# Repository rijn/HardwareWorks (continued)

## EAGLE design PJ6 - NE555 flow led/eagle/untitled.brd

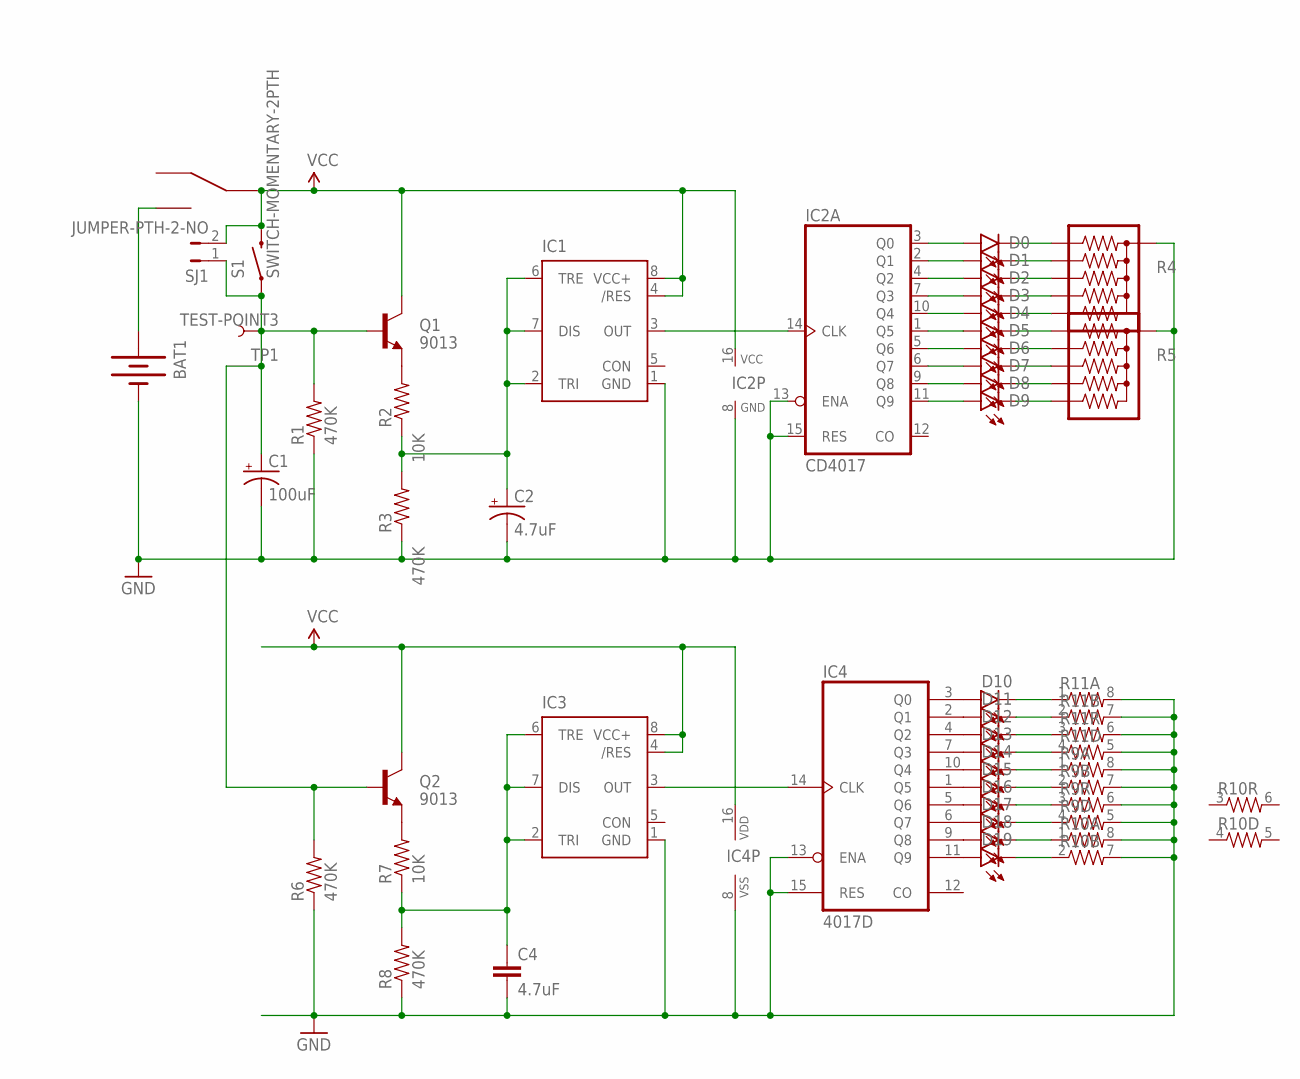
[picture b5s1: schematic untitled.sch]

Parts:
BAT1: BATTERY20PTH; BATTCOM_20MM_PTH
C1: 100uF; CPOL-RADIAL-100UF-25V
C2: 4.7uF; CPOL-RADIAL-100UF-25V
C4: 4.7uF; 0603-CAP
D0, D1, D2, D3, D4, D5, D6, D7, D8, D9: LED3MM
D10, D11, D12, D13, D14, D15, D16, D17, D18, D19: LED1206; LED-1206
IC1: NE555KIT; DIP08-KIT
IC2: CD4017; DIL16-KIT
IC3: NE555D; SO08
IC4: 4017D; SO16
Q1: 9013; TO-92-AMMO
Q2: 9013; SOT23-3
R1, R3: 470K; AXIAL-0.1
R2: 10K; AXIAL-0.1
R4, R5: RPACK-BUSSED-5-SIP-PTH-5; RPACK-SIP-PTH-5
R6, R8: 470K; 0603-RES
R7: 10K; 0603-RES
R9, R10, R11: RESISTOR-ARRAY0603-ARV; 0603-ARV
S1: SWITCH-MOMENTARY-2PTH; TACTILE-PTH
SJ1: JUMPER-PTH-2-NO; PTH-JUMPER-2-NO_NO_SILK
TP1: TEST-POINT3; PAD.03X.03
U$1: KFT; SWITCH_LOCK

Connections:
GND: BAT1.2 (-), C1.2 (-), C2.2 (-), C4.2, IC1.1 (GND), IC2.8 (GND), IC2.13 (ENA), IC2.15 (RES), IC3.1 (GND), IC4.8 (VSS), IC4.13 (ENA), IC4.15 (RES), R1.P$1 (1), R3.P$1 (1), R4.P$1 (1), R5.P$1 (1), R6.1, R8.1, R9.5 (2), R9.6 (2), R9.7 (2), R9.8 (2), R10.7 (2), R10.8 (2), R11.5 (2), R11.6 (2), R11.7 (2), R11.8 (2)
unnamed: D10.A, IC4.3 (Q0)
unnamed: C1.1 (+), Q1.2 (B), Q2.1 (B), R1.P$2 (2), R6.2, S1.1, SJ1.1, TP1.P$1
unnamed: Q2.2 (E), R7.2
unnamed: Q1.1 (E), R2.P$2 (2)
unnamed: C2.1 (+), IC1.2 (TRI), IC1.6 (TRE), IC1.7 (DIS), R2.P$1 (1), R3.P$2 (2)
unnamed: C4.1, IC3.2 (TRI), IC3.6 (TRE), IC3.7 (DIS), R7.1, R8.2
unnamed: IC3.3 (OUT), IC4.14 (CLK)
unnamed: D11.A, IC4.2 (Q1)
unnamed: D0.A, IC2.3 (Q0)
unnamed: D1.A, IC2.2 (Q1)
unnamed: D12.A, IC4.4 (Q2)
unnamed: D2.A, IC2.4 (Q2)
unnamed: IC1.3 (OUT), IC2.14 (CLK)
unnamed: D13.A, IC4.7 (Q3)
unnamed: D14.A, IC4.10 (Q4)
unnamed: D15.A, IC4.1 (Q5)
unnamed: D16.A, IC4.5 (Q6)
unnamed: D17.A, IC4.6 (Q7)
unnamed: D18.A, IC4.9 (Q8)
unnamed: D3.A, IC2.7 (Q3)
unnamed: D4.A, IC2.10 (Q4)
unnamed: D5.A, IC2.1 (Q5)
unnamed: D6.A, IC2.5 (Q6)
unnamed: D7.A, IC2.6 (Q7)
unnamed: D8.A, IC2.9 (Q8)
unnamed: D9.A, IC2.11 (Q9)
unnamed: D0.K (C), R4.P$2 (2)
unnamed: D1.K (C), R4.P$3 (3)
unnamed: D2.K (C), R4.P$4 (4)
unnamed: D3.K (C), R4.P$5 (5)
unnamed: D4.K (C), R4.P$6 (6)
unnamed: D5.K (C), R5.P$2 (2)
unnamed: D6.K (C), R5.P$3 (3)
unnamed: D7.K (C), R5.P$4 (4)
unnamed: D8.K (C), R5.P$5 (5)
unnamed: D9.K (C), R5.P$6 (6)
unnamed: D19.A, IC4.11 (Q9)
unnamed: BAT1.1 (+), U$1.S$3, U$1.S$4
unnamed: D10.C, R11.1
unnamed: D11.C, R11.2 (1)
unnamed: D12.C, R11.3 (1)
unnamed: D13.C, R11.4 (1)
unnamed: D14.C, R9.1
unnamed: D15.C, R9.2 (1)
unnamed: D16.C, R9.3 (1)
unnamed: D17.C, R9.4 (1)
unnamed: D18.C, R10.1
unnamed: D19.C, R10.2 (1)
VCC: IC1.4 (/RES), IC1.8 (VCC+), IC2.16 (VCC), IC3.4 (/RES), IC3.8 (VCC+), IC4.16 (VDD), Q1.3 (C), Q2.3 (C), S1.3 (2), SJ1.2, U$1.S$2 (P$C), U$1.S$5 (P$C)

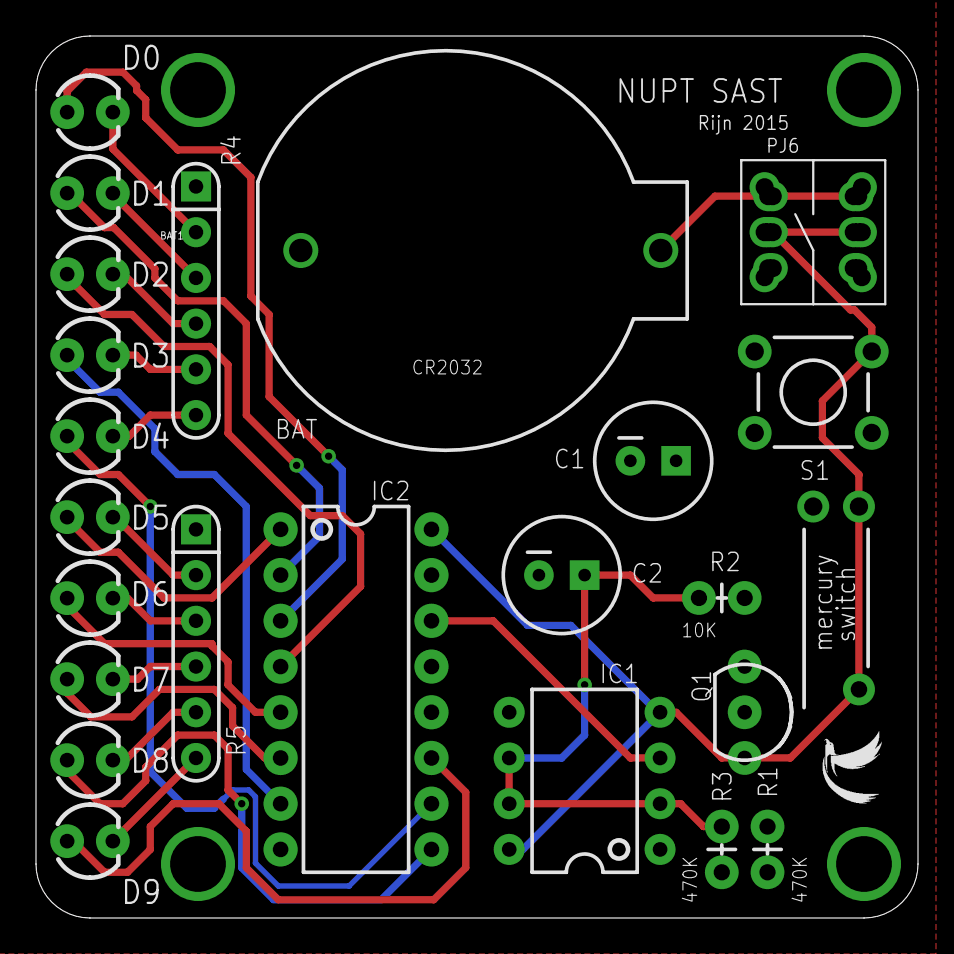
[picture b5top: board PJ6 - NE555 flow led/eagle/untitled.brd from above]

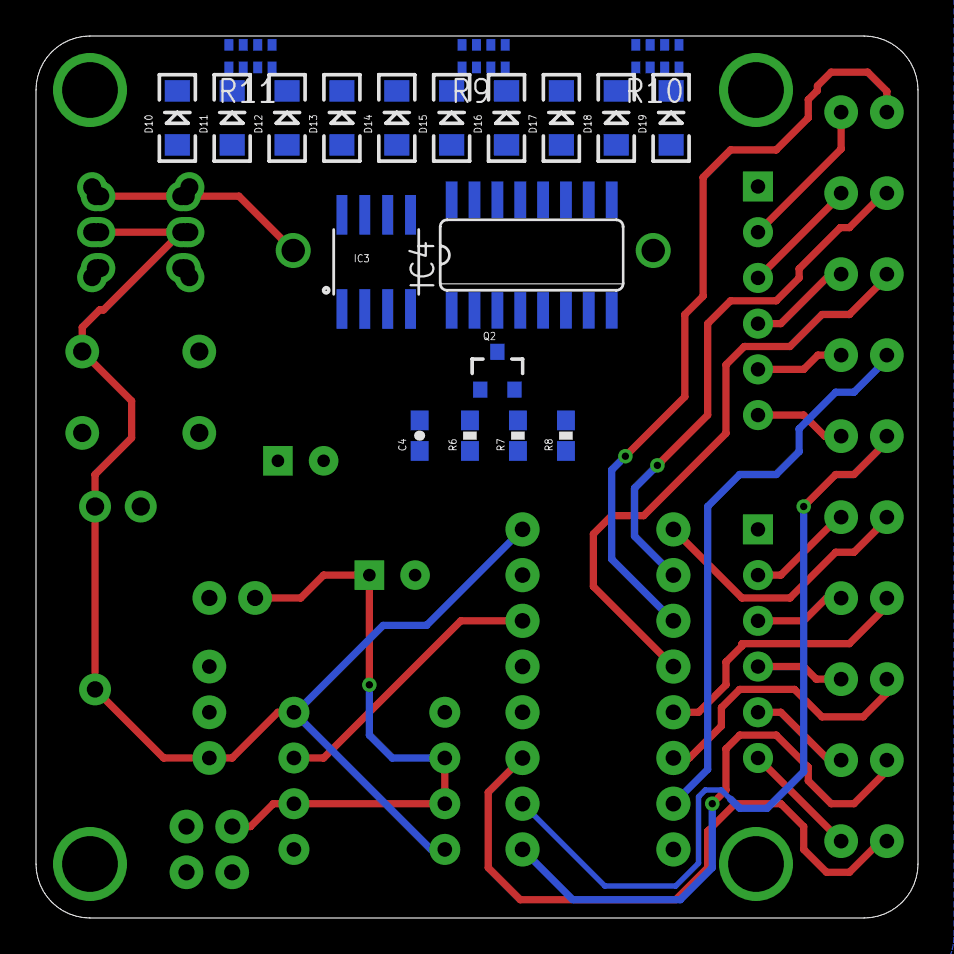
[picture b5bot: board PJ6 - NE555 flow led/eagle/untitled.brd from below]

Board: 2 copper layers, 49.0 x 49.0 mm, 46 parts (21 on the bottom side), 50 nets.

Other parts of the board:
U$2: LOGO

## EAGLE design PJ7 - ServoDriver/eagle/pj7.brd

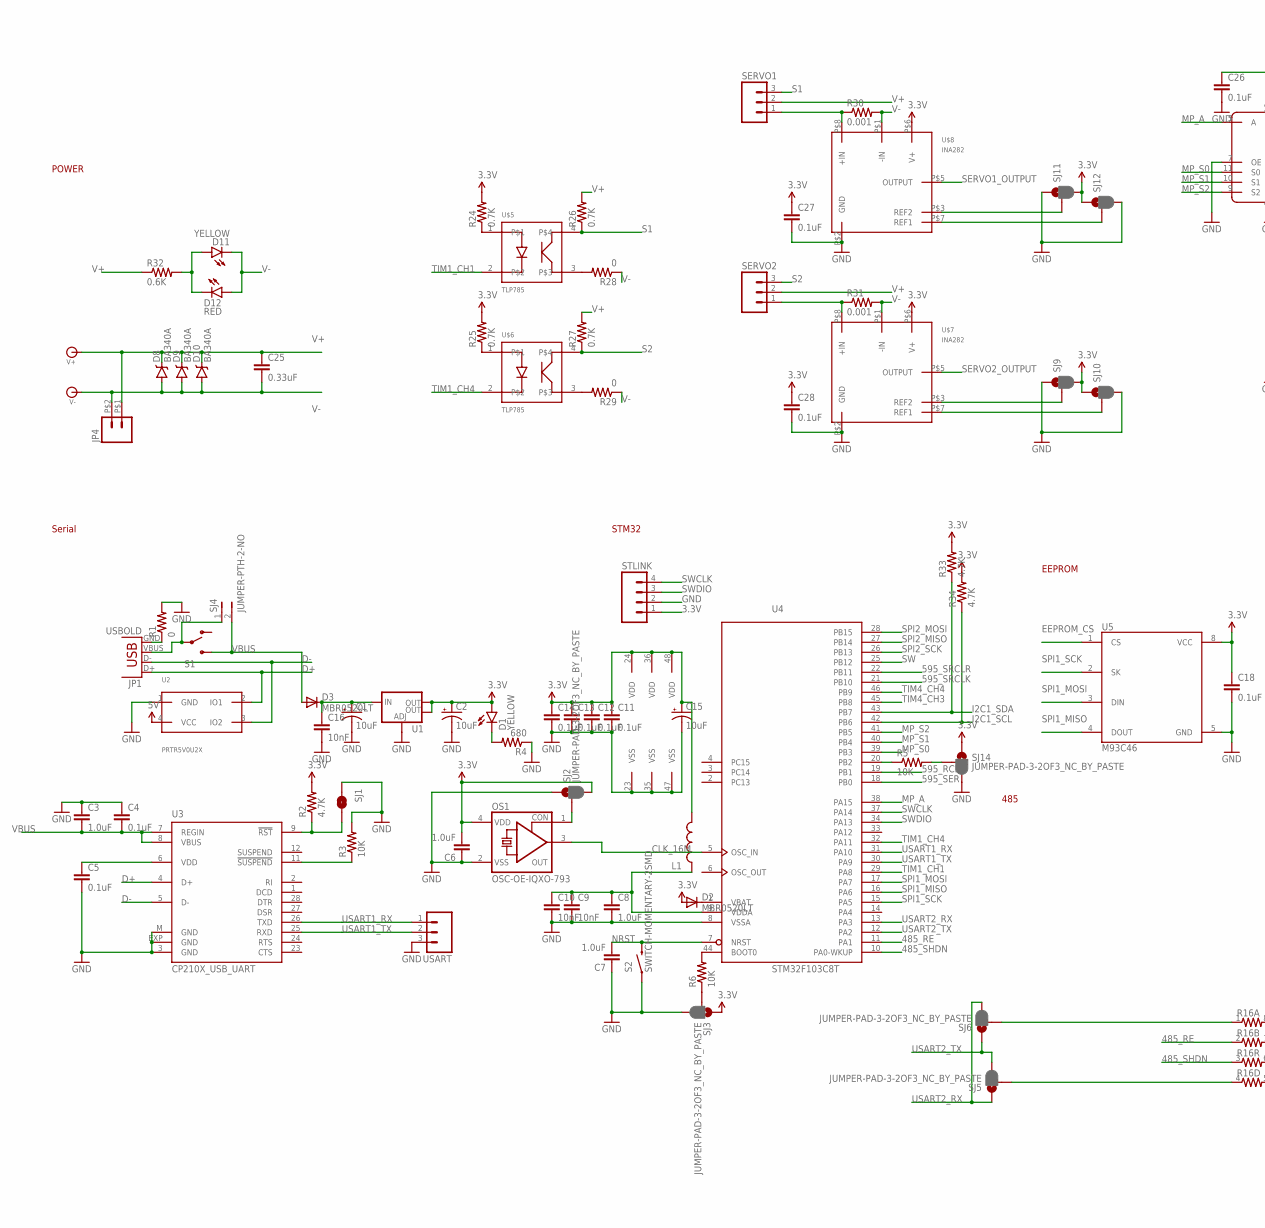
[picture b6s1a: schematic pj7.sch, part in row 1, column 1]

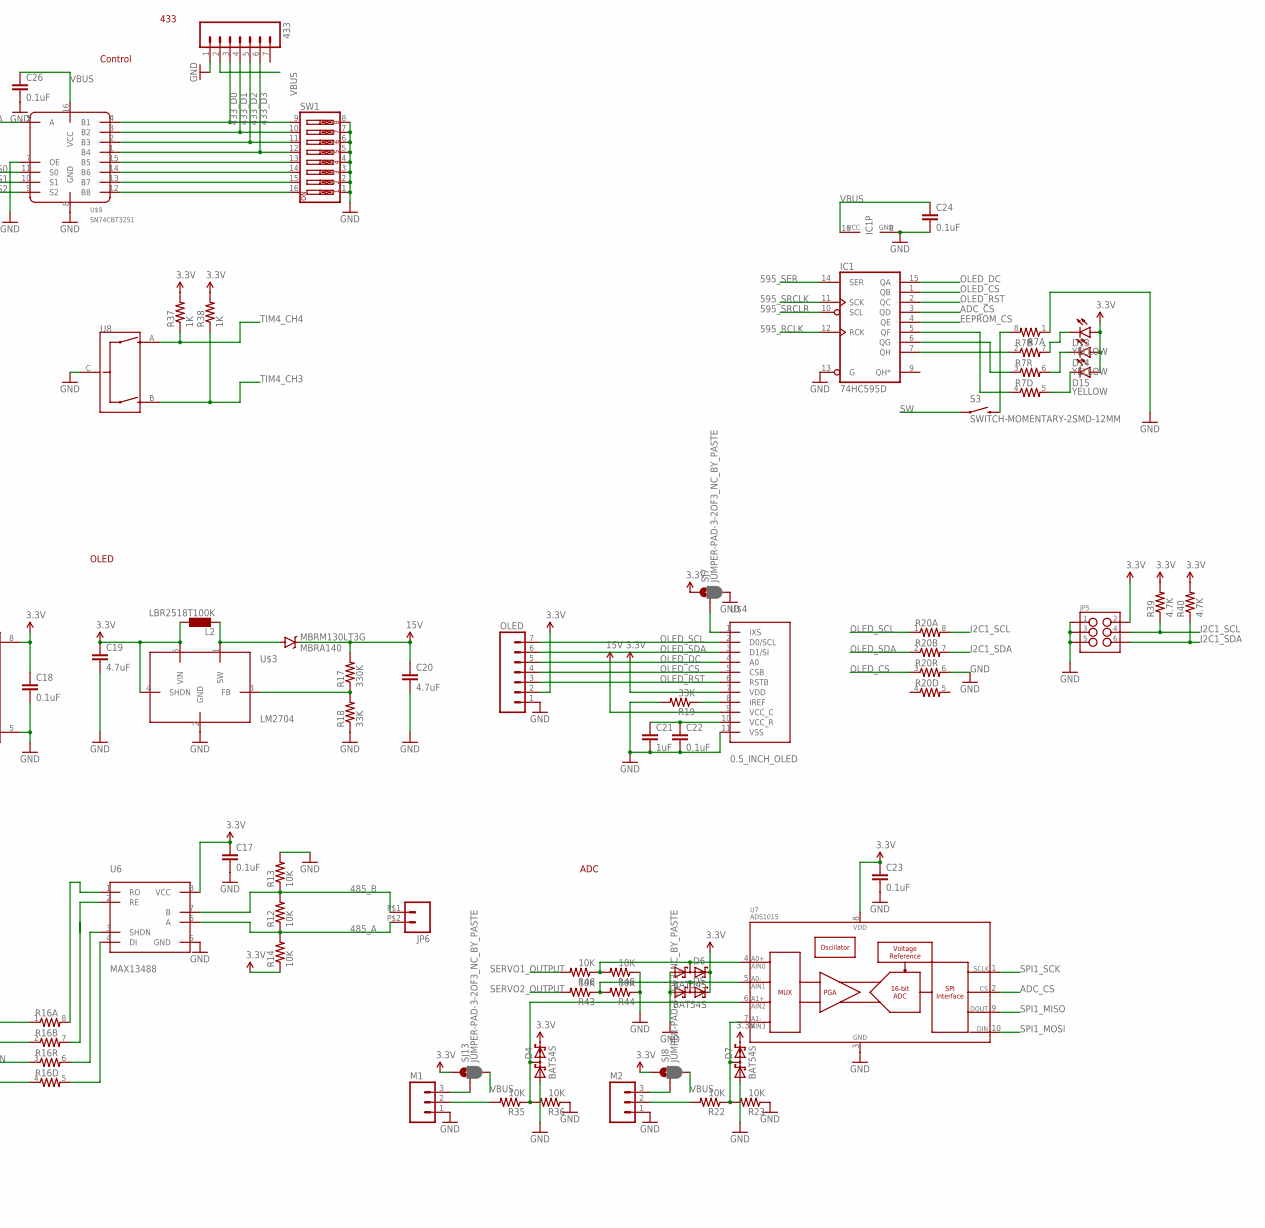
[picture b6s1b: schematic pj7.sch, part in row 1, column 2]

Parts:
433: M07LOCK; 1X07_LOCK
C1, C2, C15: 10uF; EIA3216
C3, C6, C7, C8: 1.0uF; 0603-CAP
C4, C5, C11, C12, C13, C14, C17, C18, C22, C23, C24, C26, C27, C28: 0.1uF; 0603-CAP
C9, C10, C16: 10nF; 0603-CAP
C19, C20: 4.7uF; 0603-CAP
C21: 1uF; 0603-CAP
C25: 0.33uF; 0805-CAP
D1, D11, D13, D14, D15: YELLOW; LED-1206
D2, D3: MBR0520LT; SOD123
D4, D5, D6, D7: BAT54S; SOT23
D8, D9, D10: BA340A; SMA-DIODE
D12: RED; LED-1206
IC1: 74HC595D; SO16
JP1: USBOLD; USB-MINIB-OLD
JP4, JP6: M02; 1X02_5.08
JP5: M03X2; 2X3_SMD
L1: INDUCTOR0603; 0603
L2: LBR2518T100K; L3225P
M1, M2: M03LOCK; 1X03_LOCK
MBRM130LT3G: MBRA140; SMA-DIODE
OLED: M07LOCK; 1X07_LOCK
OS1: OSC-OE-IQXO-793; 2.5X2-4-PAD
R1, R28, R29: 0; 0603
R2, R33, R34, R39, R40: 4.7K; 0603-RES
R3, R5, R6, R12, R13, R14, R22, R23, R35, R36, R43, R44, R45, R46: 10K; 0603-RES
R4: 680; 0603-RES
R7, R16, R20: RESISTOR-ARRAY0603-ARV; 0603-ARV
R17: 330K; 0603-RES
R18, R19: 33K; 0603-RES
R24, R25, R26, R27: 0.7K; 0603
R30, R31: 0.001; 2512
R32: 0.6K; 0805
R37, R38: 1K; 0603-RES
S1: SWITCH-SPDTSMD; AYZ0202
S2: SWITCH-MOMENTARY-2SMD; TACTILE-SWITCH-SMD
S3: SWITCH-MOMENTARY-2SMD-12MM; TACTILE-SMD-12MM
SERVO1, SERVO2: M03LOCK_LONGPADS; 1X03_LOCK_LONGPADS
SJ1: JUMPER-PAD-2-NOYES_SILK; PAD-JUMPER-2-NO_YES_SILK
SJ2, SJ3, SJ5, SJ6, SJ7, SJ8, SJ9, SJ10, SJ11, SJ12, SJ13, SJ14: JUMPER-PAD-3-2OF3_NC_BY_PASTE; PAD-JUMPER-3-2OF3_NC_BY_PASTE_YES_SILK_FULL_BOX
SJ4: JUMPER-PTH-2-NO; PTH-JUMPER-2-NO_NO_SILK
STLINK: M04LOCK; 1X04_LOCK
SW1: SW_DIP-8-SMT-HALFSIZE; DIPSWITCH-08-50MIL
U1: V_REG_LM1117SOT223; SOT223
U2: PRTR5V0U2X; SOT143
U3: CP210X_USB_UART; MLP28
U4: STM32F103C8T; LQFP48
U5: M93C46; SO08
U6: MAX13488; SOIC8
U7: ADS1015; MSOP10
U8: ENCODER-QUADRATURE; ENCODER-16MM-QUAD
U$3: LM2704; SOT23-5
U$4: 0.5_INCH_OLED; BL125-11RL-TAGF
U$5, U$6: TLP785; DIL04
U$7, U$8: INA282; SOP8
U$9: SN74CBT3251; TSSOP16
USART: M03LOCK; 1X03_LOCK
V+: BANANA_CONN
V-: BANANA_CONN

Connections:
3.3V: C2.A (+), C6.2, C11.1, C12.1, C13.1, C14.1, C15.A (+), C17.1, C18.1, C19.1, C23.1, C27.1, C28.1, D1.A, D2.A, D4.2 (C2), D5.2 (C2), D6.2 (C2), D7.2 (C2), D13.A, D14.A, D15.A, JP5.2, L1.2, L2.1, OLED.2, OS1.4 (VDD), R2.2, R14.1, R24.2, R25.2, R33.2, R34.2, R37.2, R38.2, R39.2, R40.2, SJ2.3, SJ3.1, SJ7.1, SJ8.1, SJ9.3, SJ10.1, SJ11.3, SJ12.1, SJ13.1, SJ14.1, STLINK.1, U1.2 (OUT), U1.4 (OUT), U4.24 (VDD), U4.36 (VDD), U4.48 (VDD), U5.8 (VCC), U6.8 (VCC), U7.8 (VDD), U$3.4 (SHDN), U$3.5 (VIN), U$4.7 (VDD), U$7.P$6 (V+), U$8.P$6 (V+)
5V: U2.4 (VCC)
15V: C20.1, MBRM130LT3G.C, R17.2, U$4.9 (VCC_C)
433_D0: 433.3, SW1.9, U$9.4 (B1)
433_D1: 433.4, SW1.10, U$9.3 (B2)
433_D2: 433.5, SW1.11, U$9.2 (B3)
433_D3: 433.6, SW1.12, U$9.1 (B4)
485_A: JP6.P$2 (2), R12.1, R14.2, U6.6 (A)
485_B: JP6.P$1 (1), R12.2, R13.1, U6.7 (B)
485_RE: R16.2 (1), U4.11 (PA1)
485_SHDN: R16.3 (1), U4.10 (PA0-WKUP)
595_RCLK: IC1.12 (RCK), U4.19 (PB1)
595_SER: IC1.14 (SER), U4.18 (PB0)
595_SRCLK: IC1.11 (SCK), U4.21 (PB10)
595_SRCLR: IC1.10 (SCL), U4.22 (PB11)
ADC_CS: IC1.3 (QD), U7.2 (CS)
CLK_16M: OS1.3 (OUT), U4.5 (OSC_IN)
D+: JP1.D+, U2.2 (IO1), U3.4 (D+)
D-: JP1.D-, U2.3 (IO2), U3.5 (D-)
EEPROM_CS: IC1.4 (QE), U5.1 (CS)
GND: 433.1, C1.C (-), C2.C (-), C3.1, C4.1, C5.2, C6.1, C7.1, C8.2, C9.2, C10.2, C11.2, C12.2, C13.2, C14.2, C15.C (-), C16.2, C17.2, C18.2, C19.2, C20.2, C21.2, C22.2, C23.2, C24.2, C26.2, C27.2, C28.2, D4.1 (A1), D5.1 (A1), D6.1 (A1), D7.1 (A1), IC1.8 (GND), IC1.13 (G), JP5.1, JP5.3, JP5.5, M1.1, M2.1, OLED.1, OS1.2 (VSS), R1.2, R3.2, R4.1, R7.1, R13.2, R18.1, R19.2, R20.6 (2), R23.1, R36.1, R44.1, R45.1, S2.1, SJ1.2, SJ2.1, SJ3.3, SJ7.3, SJ9.1, SJ10.3, SJ11.1, SJ12.3, SJ14.3, STLINK.2, SW1.1, SW1.2, SW1.3, SW1.4, SW1.5, SW1.6, SW1.7, SW1.8, U1.1 (ADJ), U2.1 (GND), U3.3 (GND), U3.EXP (GND), U3.M (GND), U4.8 (VSSA), U4.23 (VSS), U4.35 (VSS), U4.47 (VSS), U5.5 (GND), U6.5 (GND), U7.3 (VSS), U8.C, U$3.2 (GND), U$4.11 (VSS), U$7.P$2 (GND), U$8.P$2 (GND), U$9.7 (OE), U$9.8 (GND), USART.3
I2C1_SCL: JP5.4, R20.8 (2), R34.1, R39.1, U4.42 (PB6)
I2C1_SDA: JP5.6, R20.7 (2), R33.1, R40.1, U4.43 (PB7)
MP_A: U4.38 (PA15), U$9.5 (A)
MP_S0: U4.39 (PB3), U$9.11 (S0)
MP_S1: U4.40 (PB4), U$9.10 (S1)
MP_S2: U4.41 (PB5), U$9.9 (S2)
unnamed: JP1.GND, R1.1
unnamed: R3.1, U3.11 (!SUSPEND)
unnamed: D1.C, R4.2
unnamed: D2.C, U4.1 (VBAT)
unnamed: JP1.VBUS, S1.2, SJ4.1
unnamed: C8.1, C9.1, C10.1, L1.1, U4.9 (VDDA)
unnamed: R6.2, U4.44 (BOOT0)
unnamed: R6.1, SJ3.2
unnamed: R2.1, SJ1.1, U3.9 (!RST)
unnamed: OS1.1 (CON), SJ2.2
unnamed: C1.A (+), C16.1, D3.C, U1.3 (IN)
unnamed: R17.1, R18.2, U$3.3 (FB)
unnamed: C5.1, U3.6 (VDD)
unnamed: IC1.7 (QH), R7.2 (1)
unnamed: IC1.6 (QG), R7.3 (1)
unnamed: L2.2, MBRM130LT3G.A, U$3.1 (SW)
unnamed: IC1.5 (QF), R7.4 (1)
unnamed: C21.1, C22.1, U$4.10 (VCC_R)
unnamed: SJ7.2, U$4.1 (IXS)
unnamed: D15.C, R7.5 (2)
unnamed: D14.C, R7.6 (2)
unnamed: R16.8 (2), U6.1 (RO)
unnamed: R16.6 (2), U6.3 (SHDN)
unnamed: R16.5 (2), U6.4 (DI)
unnamed: R16.7 (2), U6.2 (RE)
unnamed: R16.1, SJ6.2
unnamed: R24.1, U$5.1
unnamed: M2.2, R22.2
unnamed: R16.4 (1), SJ5.2
unnamed: R19.1, U$4.8 (IREF)
unnamed: D7.3 (C1A2), R22.1, R23.2, U7.7 (AIN3)
unnamed: R25.1, U$6.1
unnamed: R30.1, SERVO1.1, U$8.P$8 (+IN)
unnamed: M2.3, SJ8.2
unnamed: R31.1, SERVO2.1, U$7.P$8 (+IN)
unnamed: R28.2, U$5.3
unnamed: R29.2, U$6.3
unnamed: SJ9.2, U$7.P$3 (REF2)
unnamed: SJ10.2, U$7.P$7 (REF1)
unnamed: SJ11.2, U$8.P$3 (REF2)
unnamed: SJ12.2, U$8.P$7 (REF1)
unnamed: D11.A, D12.C, R32.2
unnamed: M1.3, SJ13.2
unnamed: D4.3 (C1A2), R35.1, R36.2, U7.6 (AIN2)
unnamed: M1.2, R35.2
unnamed: R5.2, SJ14.2
unnamed: D5.3 (C1A2), R43.1, R44.2, U7.5 (AIN1)
unnamed: D6.3 (C1A2), R45.2, R46.1, U7.4 (AIN0)
unnamed: SW1.13, U$9.15 (B5)
unnamed: SW1.14, U$9.14 (B6)
unnamed: SW1.15, U$9.13 (B7)
unnamed: SW1.16, U$9.12 (B8)
unnamed: D13.C, R7.7 (2)
unnamed: R7.8 (2), S3.3 (2)
NRST: C7.2, S2.3 (2), U4.7 (NRST)
OLED_CS: IC1.1 (QB), OLED.4, R20.3 (1), U$4.5 (CSB)
OLED_DC: IC1.15 (QA), OLED.5, U$4.4 (A0)
OLED_RST: IC1.2 (QC), OLED.3, U$4.6 (RSTB)
OLED_SCL: OLED.7, R20.1, U$4.2 (D0/SCL)
OLED_SDA: OLED.6, R20.2 (1), U$4.3 (D1/SI)
OURET: R5.1, U4.20 (PB2)
S1: R26.1, SERVO1.3, U$5.4
S2: R27.1, SERVO2.3, U$6.4
SERVO1_OUTPUT: R46.2, U$8.P$5 (OUTPUT)
SERVO2_OUTPUT: R43.2, U$7.P$5 (OUTPUT)
SPI1_MISO: U4.16 (PA6), U5.4 (DOUT), U7.9 (DOUT/DRDY)
SPI1_MOSI: U4.17 (PA7), U5.3 (DIN), U7.10 (DIN)
SPI1_SCK: U4.15 (PA5), U5.2 (SK), U7.1 (SCLK)
SPI2_MISO: U4.27 (PB14)
SPI2_MOSI: U4.28 (PB15)
SPI2_SCK: U4.26 (PB13)
SW: S3.1, U4.25 (PB12)
SWCLK: STLINK.4, U4.37 (PA14)
SWDIO: STLINK.3, U4.34 (PA13)
TIM1_CH1: U4.29 (PA8), U$5.2
TIM1_CH4: U4.32 (PA11), U$6.2
TIM4_CH3: R38.1, U4.45 (PB8), U8.B
TIM4_CH4: R37.1, U4.46 (PB9), U8.A
USART1_RX: U3.26 (TXD), U4.31 (PA10), USART.1
USART1_TX: U3.25 (RXD), U4.30 (PA9), USART.2
USART2_RX: SJ5.1, SJ6.3, U4.13 (PA3)
USART2_TX: SJ5.3, SJ6.1, U4.12 (PA2)
V+: C25.1, D8.C, D9.C, D10.C, JP4.P$1 (1), R26.2, R27.2, R32.1, SERVO1.2, SERVO2.2, V+.P$1
V-: C25.2, D8.A, D9.A, D10.A, D11.C, D12.A, JP4.P$2 (2), R28.1, R29.1, R30.2, R31.2, U$7.P$1 (-IN), U$8.P$1 (-IN), V-.P$1
VBUS: 433.2, C3.2, C4.2, C24.1, C26.1, D3.A, IC1.16 (VCC), S1.3 (S), SJ4.2, SJ8.3, SJ13.3, U3.7 (REGIN), U3.8 (VBUS), U$9.16 (VCC)

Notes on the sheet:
OLED
EEPROM
485
POWER
STM32
Serial
ADC
Control
433

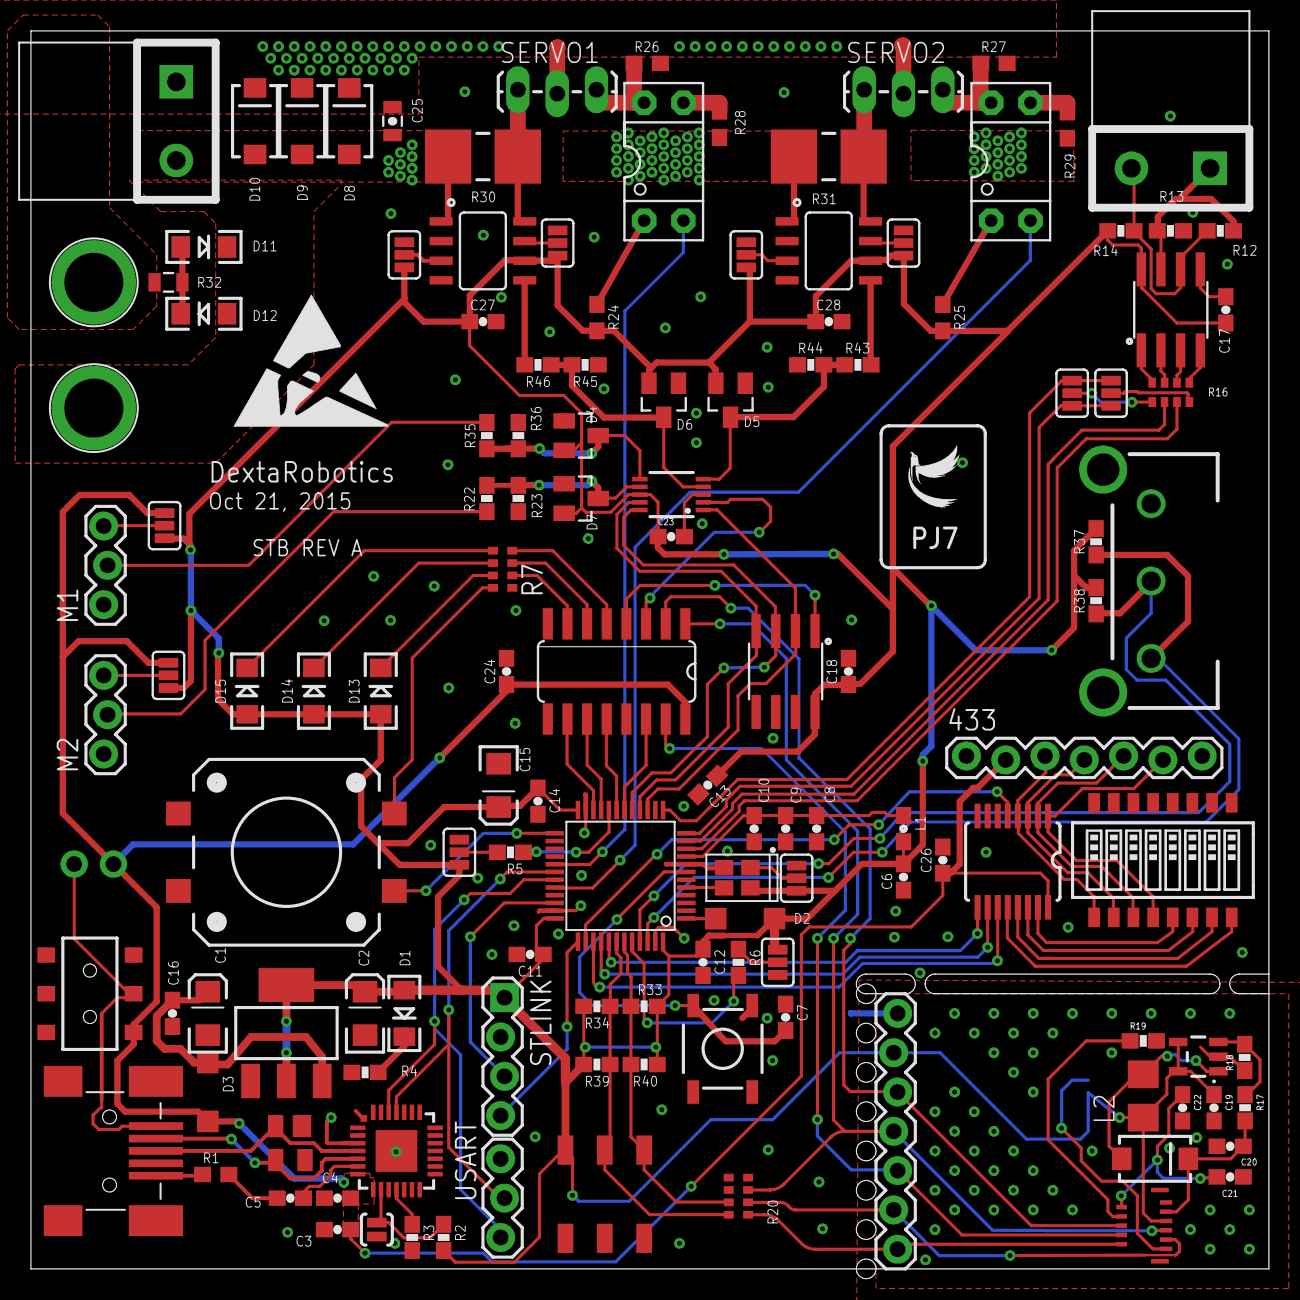
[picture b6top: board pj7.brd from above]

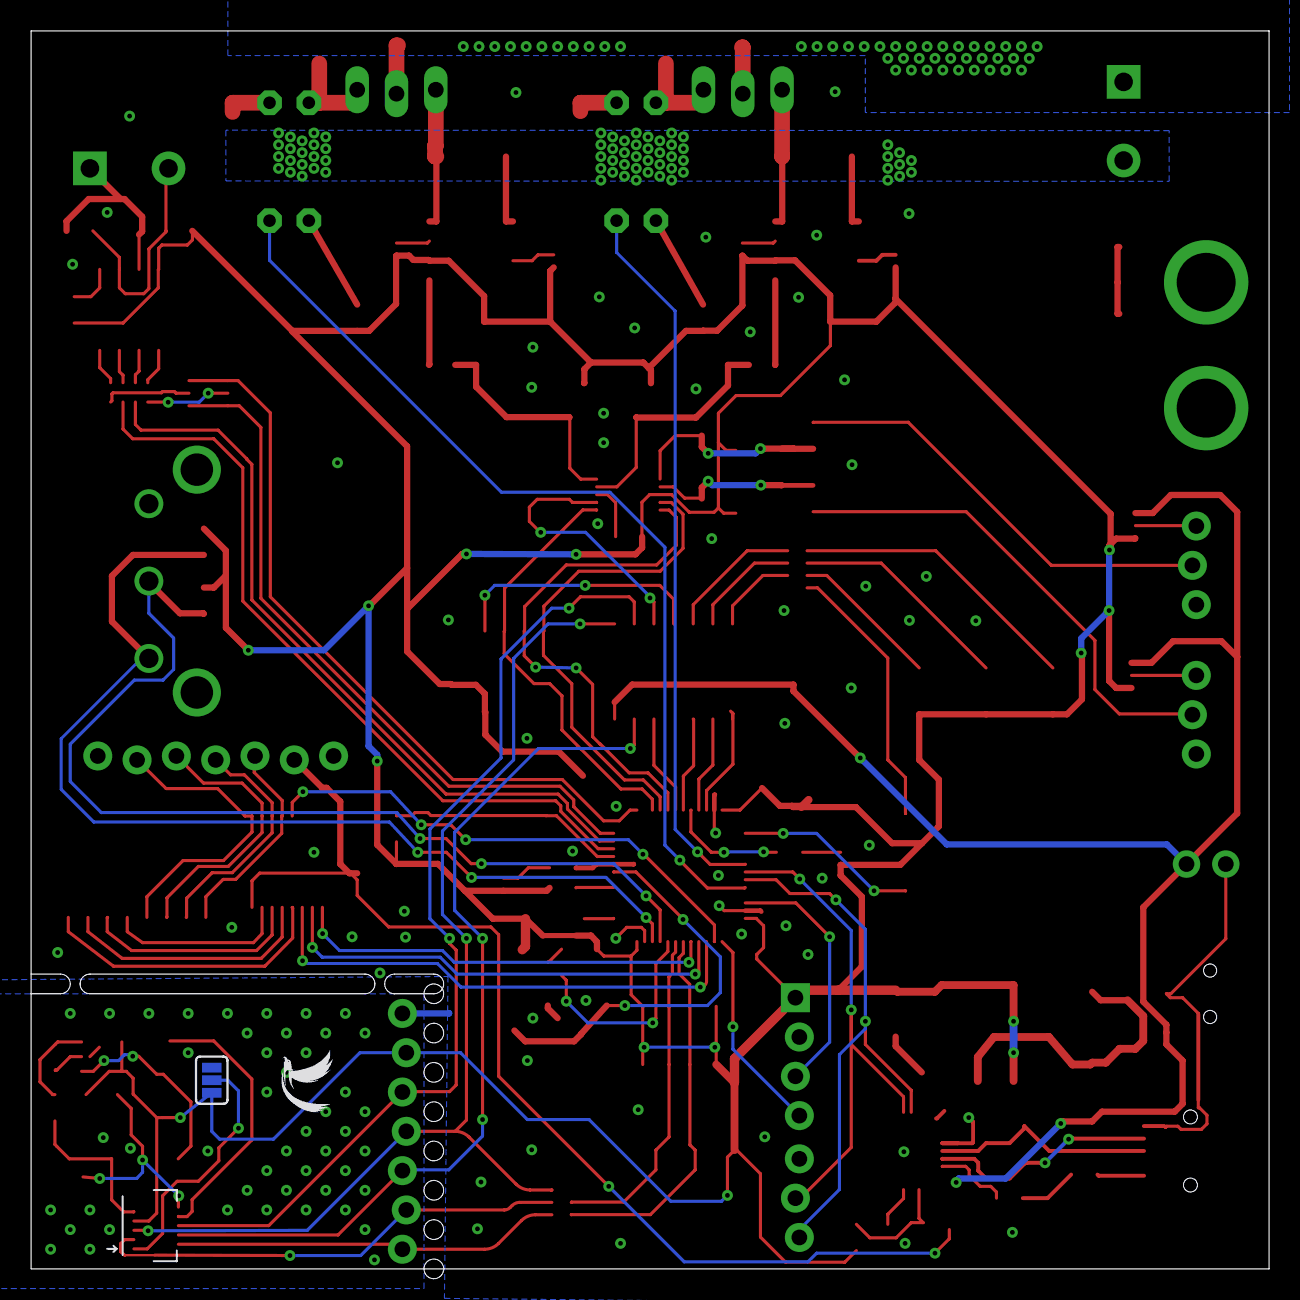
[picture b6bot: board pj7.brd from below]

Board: 2 copper layers, 80.0 x 80.0 mm, 136 parts (2 on the bottom side), 108 nets.

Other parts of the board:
U$1, U$2: LOGO
U$10: ESD_10.00

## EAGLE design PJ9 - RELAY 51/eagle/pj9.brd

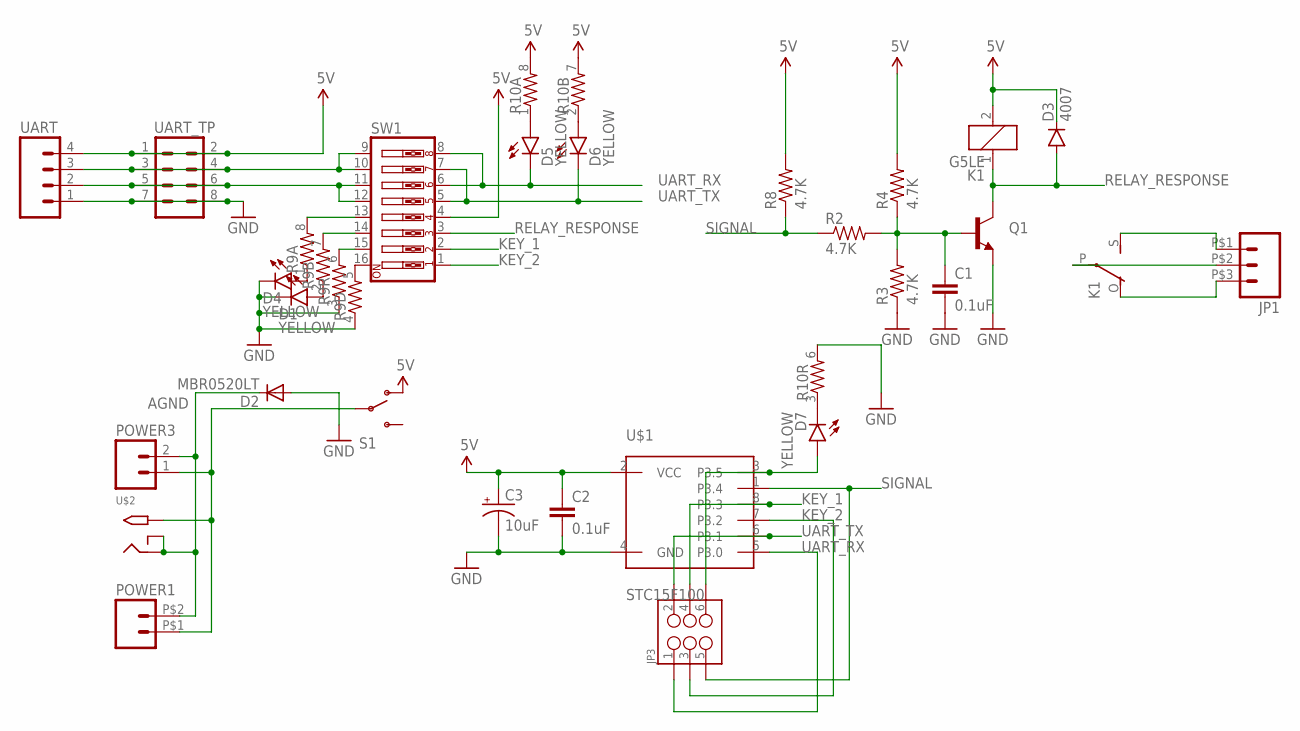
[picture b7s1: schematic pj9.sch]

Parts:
C1, C2: 0.1uF; 0603-CAP
C3: 10uF; EIA3216
D1, D4, D5, D6, D7: YELLOW; LED-1206
D2: MBR0520LT; SOD123
D3: 4007; SMA-DIODE_ALT
JP1: M035.08; 1X03_5.08
JP3: M03X2; 2X3_SMD
K1: G5LE
POWER1: M02; 1X02_5.08
POWER3: M02LOCK; 1X02_LOCK
Q1: TRANSISTOR_NPNSOT23-3; SOT23-3
R2, R3, R4, R8: 4.7K; 0603-RES
R9, R10: RESISTOR-ARRAY0603-ARV; 0603-ARV
S1: SWITCH-SPDTSMD; AYZ0202
SW1: SW_DIP-8-SMT-HALFSIZE; DIPSWITCH-08-50MIL
U$1: STC15F100; SO08-TIGHT
U$2: 2.1MMJACK; PJ-102A
UART: M04LOCK; 1X04_LOCK
UART_TP: M04X2SMD; 2X4_SMD

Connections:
5V: C2.1, C3.A (+), D3.C, K1.2, R4.2, R8.2, R10.7 (2), R10.8 (2), S1.1 (O), SW1.4, U$1.2 (VCC), UART.4, UART_TP.1, UART_TP.2
AGND: D2.C, POWER1.P$2 (2), POWER3.2, U$2.RING, U$2.RING_SW
GND: C1.2, C2.2, C3.C (-), D1.C, D2.A, D4.C, Q1.2 (E), R3.1, R9.3 (1), R9.4 (1), R10.6 (2), U$1.4 (GND), UART.1, UART_TP.7, UART_TP.8
KEY_1: JP3.4, SW1.2, U$1.8 (P3.3)
KEY_2: JP3.3, SW1.1, U$1.7 (P3.2)
unnamed: SW1.11, SW1.12, UART.2, UART_TP.5, UART_TP.6
unnamed: R9.8 (2), SW1.13
unnamed: R9.5 (2), SW1.16
unnamed: SW1.9, SW1.10, UART.3, UART_TP.3, UART_TP.4
unnamed: C1.1, Q1.1 (B), R2.2, R3.2, R4.1
unnamed: R9.7 (2), SW1.14
unnamed: JP1.P$2 (2), K1.P
unnamed: JP1.P$1 (1), K1.S
unnamed: JP1.P$3 (3), K1.O
unnamed: R9.6 (2), SW1.15
unnamed: D5.A, R10.1
unnamed: D6.A, R10.2 (1)
unnamed: D4.A, R9.1
unnamed: D1.A, R9.2 (1)
unnamed: POWER1.P$1 (1), POWER3.1, S1.2, U$2.TIP
unnamed: D7.C, R10.3 (1)
unnamed: D7.A, JP3.6, U$1.3 (P3.5)
RELAY_RESPONSE: D3.A, K1.1, Q1.3 (C), SW1.3
SIGNAL: JP3.5, R2.1, R8.1, U$1.1 (P3.4)
UART_RX: D5.C, JP3.1, SW1.6, SW1.8, U$1.5 (P3.0)
UART_TX: D6.C, JP3.2, SW1.5, SW1.7, U$1.6 (P3.1)

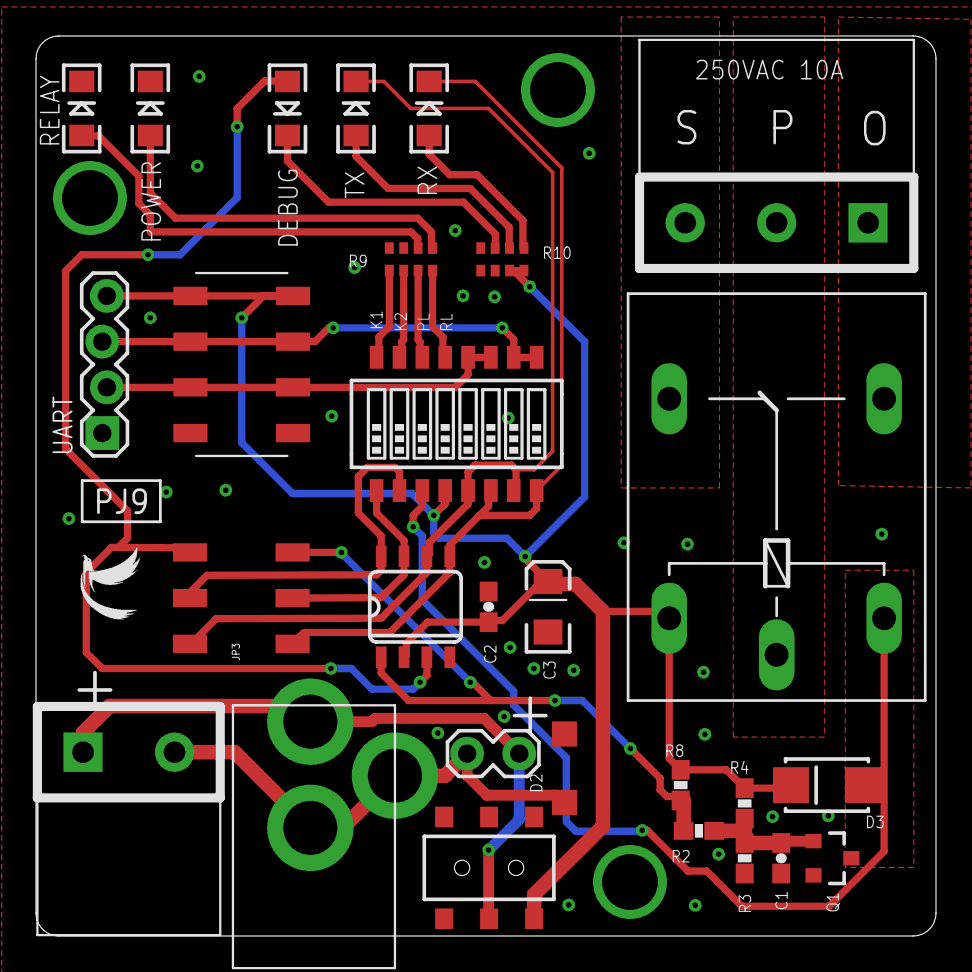
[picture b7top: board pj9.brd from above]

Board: 2 copper layers, 50.0 x 50.0 mm, 29 parts (0 on the bottom side), 26 nets.

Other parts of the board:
U$3: LOGO

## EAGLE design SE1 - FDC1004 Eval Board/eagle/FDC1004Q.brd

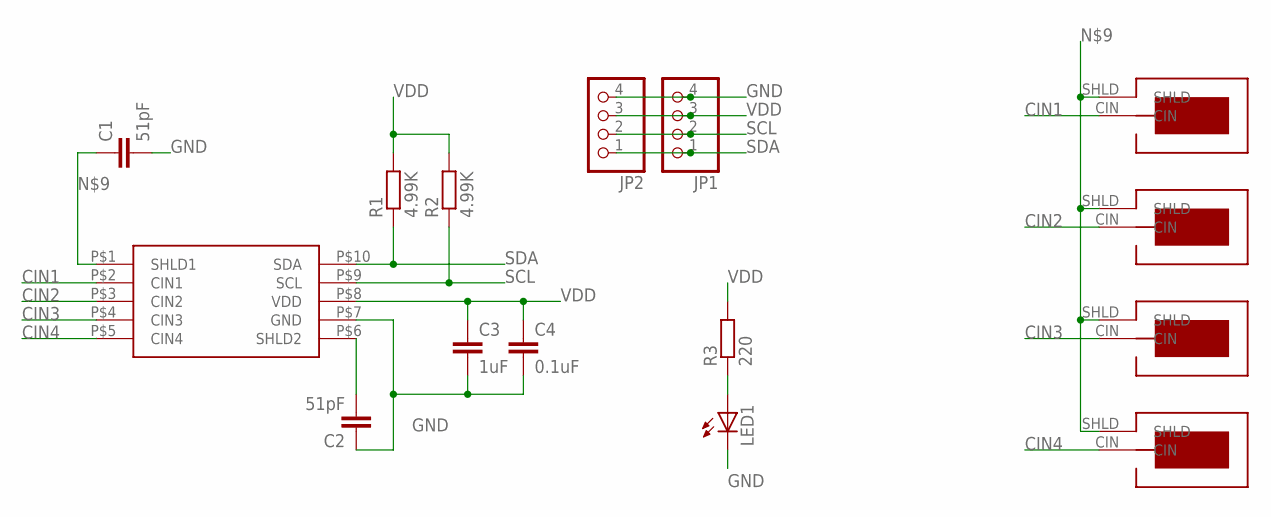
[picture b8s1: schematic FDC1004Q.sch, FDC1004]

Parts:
C1, C2: 51pF; C0805
C3: 1uF; C0805
C4: 0.1uF; C0805
JP1, JP2: PINHD-1X4; 1X04
LED1: LED_ESML0603; LED_SML0603
R1, R2: 4.99K; R0805
R3: 220; R0805
SENSOR1, SENSOR2, SENSOR3, SENSOR4: SENSOR; SENSOR_1X1
U$1: FDC1004Q; DGS

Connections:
CIN1: SENSOR1.CIN, U$1.P$2 (CIN1)
CIN2: SENSOR2.CIN, U$1.P$3 (CIN2)
CIN3: SENSOR3.CIN, U$1.P$4 (CIN3)
CIN4: SENSOR4.CIN, U$1.P$5 (CIN4)
GND: C1.2, C2.1, C3.2, C4.2, JP1.4, JP2.4, LED1.C, U$1.P$7 (GND)
unnamed: LED1.A, R3.1
unnamed: C2.2, U$1.P$6 (SHLD2)
unnamed: C1.1, SENSOR1.SHLD, SENSOR2.SHLD, SENSOR3.SHLD, SENSOR4.SHLD, U$1.P$1 (SHLD1)
SCL: JP1.2, JP2.2, R2.1, U$1.P$9 (SCL)
SDA: JP1.1, JP2.1, R1.1, U$1.P$10 (SDA)
VDD: C3.1, C4.1, JP1.3, JP2.3, R1.2, R2.2, R3.2, U$1.P$8 (VDD)

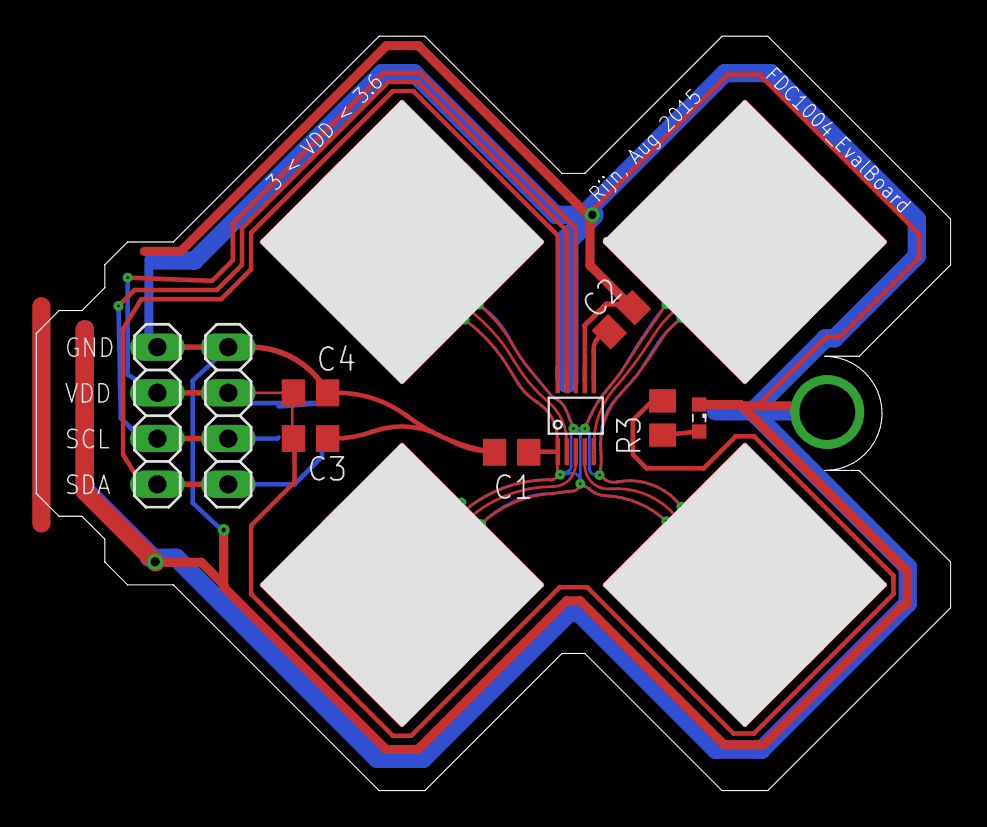
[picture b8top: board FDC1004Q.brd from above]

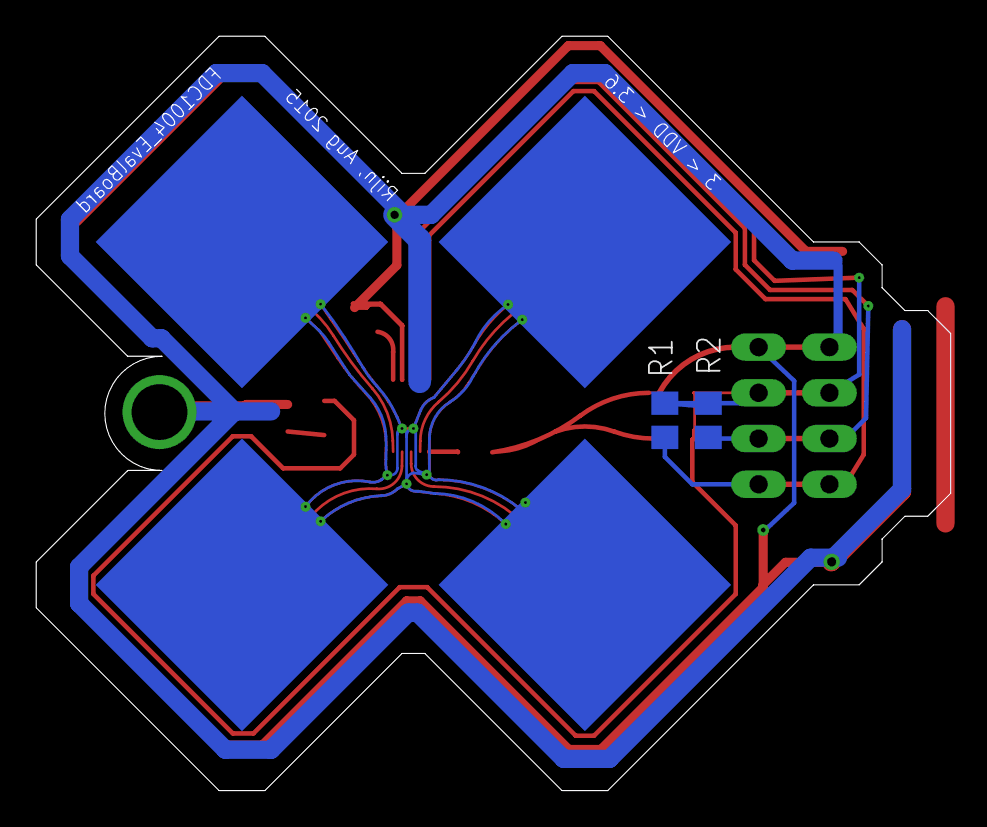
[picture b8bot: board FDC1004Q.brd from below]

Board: 2 copper layers, 50.8 x 41.9 mm, 15 parts (2 on the bottom side), 11 nets.
